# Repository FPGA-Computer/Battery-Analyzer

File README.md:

This is a Dual Channel Battery Analyzer for HaD 2015 Contest Entry.

+ Ver 2.1 Rel 0/	
|  |Initial PCB release - first layout/non-tested
|  |
|  + Eagle PCB/
|  | Eagle CAd files
|  |
|  + Sketch3D/
|  | Sketch3D model
|  |
|  + LTSpice/
|    Linear Tech Spice Simulation analog file
|
+ Windows/
| Pelles C Project file
|
+ Firmware/
  Simplicity Studio files

Hackaday project page is at 
https://hackaday.io/project/4993-dual-channel-battery-chargeranalyzer

The hardware design is under a Creative Commons Attribution-
NonCommercial-ShareAlike 4.0 International License.

The full detail of this license is available at: 
http://creativecommons.org/licenses/by-nc-sa/4.0/

The software is under Mozilla Public License
The full detail of this license is available at: 
https://www.mozilla.org/MPL/

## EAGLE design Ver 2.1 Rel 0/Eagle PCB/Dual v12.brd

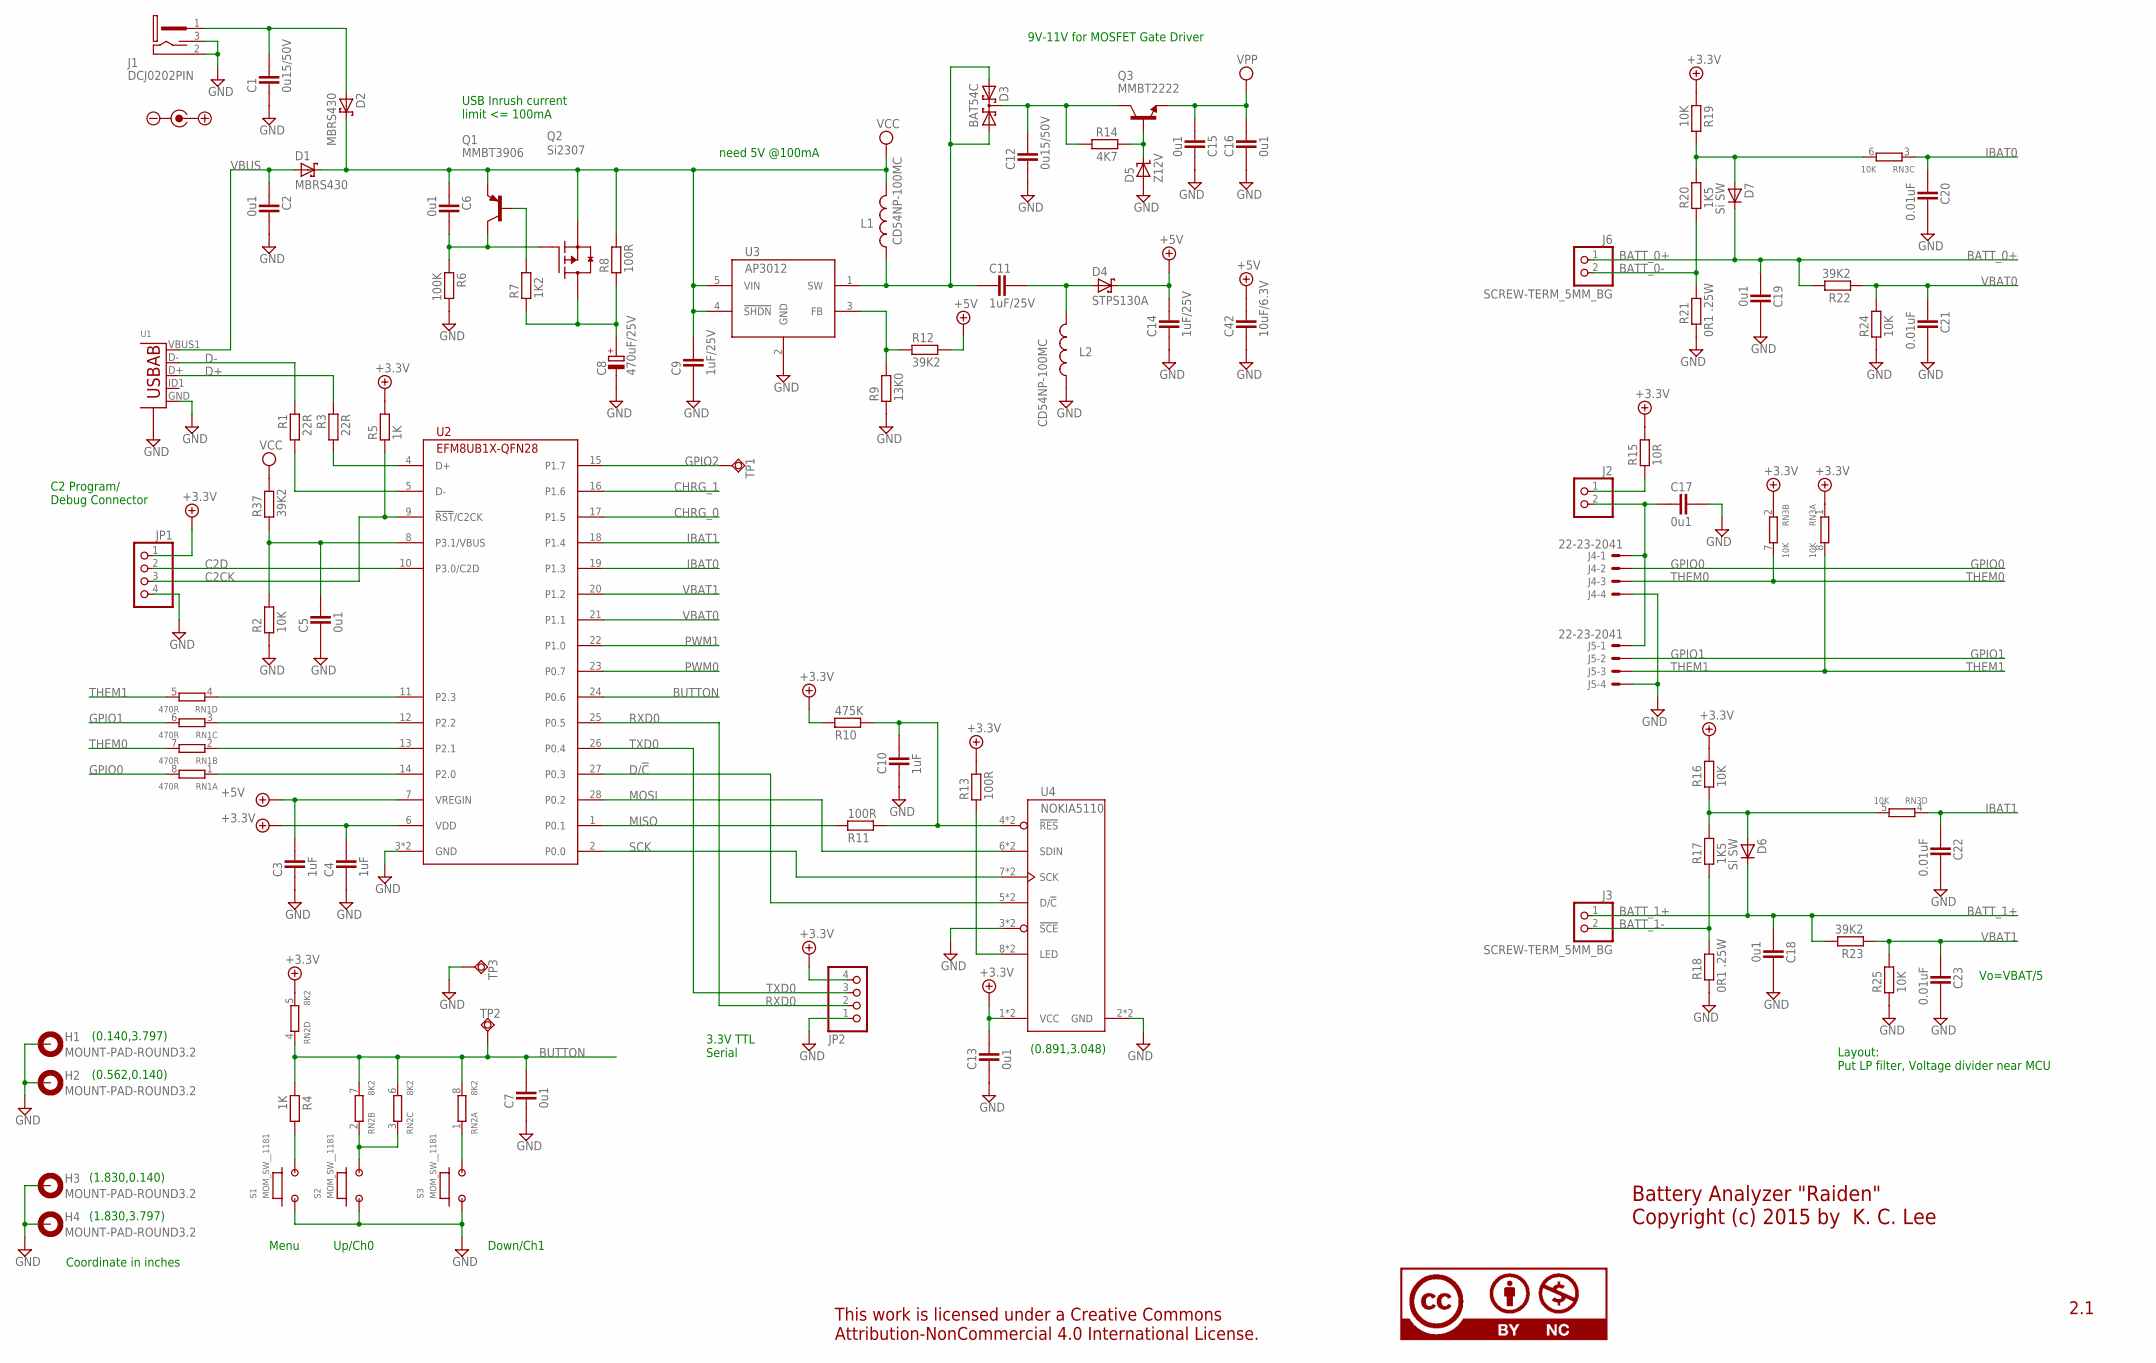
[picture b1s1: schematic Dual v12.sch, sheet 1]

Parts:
C1, C12: 0u15/50V; CAP2012X70N; PARTNO STOCK: 0.15UF/50V10%
C2, C6, C7, C13, C15, C16, C17, C18, C19: 0u1; CAPC1608X92N; PARTNO STOCK: DK 490-1532-1-ND
C3, C4: 1uF; CAPC1005X60N; PARTNO DK: 490-10435-1-ND
C5: 0u1; CAPC1005X60N; PARTNO STOCK: DK 587-1227-1-ND
C8: 470uF/25V; CAPAE1030X1020N; PARTNO STOCK
C9, C11, C14: 1uF/25V; CAP2012X70N; PARTNO DK: 311-1456-1-ND
C10: 1uF; CAPC1608X92N; PARTNO STOCK: 1UF/10V 20% TDK
C20, C21, C22, C23: 0.01uF; CAPC1608X92N; PARTNO DK: 311-1085-1-ND
C42: 10uF/6.3V; CAP2012X70N; PARTNO DK: 490-5525-1-ND
D1, D2: MBRS430; DIOM7959X265N; PARTNO STOCK
D3: BAT54C; SOT95P280X135-3N; PARTNO STOCK
D4: STPS130A; DIOM5326X292N; PARTNO DK: 497-3755-1-ND
D5: Z12V; SOT95P280X135-3N; PARTNO STOCK
D6, D7: Si SW; SOT95P280X135-3N; PARTNO STOCK: BAV99
H1, H2, H3, H4: MOUNT-PAD-ROUND3.2; 3,2-PAD; PARTNO *
J1: DCJ0202PIN; PJ-102A; PARTNO STOCK: DK CP-102A-ND
J2: PINHD-1X2_2.54; 1X02; PARTNO BG: SKU038984
J3, J6: SCREW-TERM_5MM_BG; 1X02-5MM-BG; PARTNO BG: SKU170379
J4, J5: 22-23-2041; PARTNO DK: A19431-ND
JP1: PINHD-1X4_2.54; 1X04; PARTNO BG: SKU038984
JP2: PINHD-1X4_2.54-90°; 1X04-RA; PARTNO STOCK
L1, L2: CD54NP-100MC; CD54; PARTNO DK: 587-1626-1-ND
Q1: MMBT3906; SOT95P280X135-3N; PARTNO STOCK:MMBT3906
Q2: Si2307; SOT95P280X135-3N; PARTNO STOCK: SI2307DS
Q3: MMBT2222; SOT95P280X135-3N; PARTNO STOCK: MMBT2222
R1, R3: 22R; RESC1608X55N; PARTNO STOCK: DK 1276-3497-1-ND
R2, R16, R19, R24, R25: 10K; RESC1608X55N; PARTNO STOCK: 10K 1%
R4: 1K; RESC1608X55N; PARTNO STOCK: DK 1276-3484-1-ND
R5: 1K; RESC1005X40AN; PARTNO DK: 311-1.00KLRCT-ND
R6: 100K; RESC1608X55N; PARTNO STOCK: DK311-100KHRCT-ND
R7: 1K2; RESC1608X55N; PARTNO STOCK: 1K21 1%
R8: 100R; RESC2012X70N; PARTNO STOCK
R9: 13K0; RESC1608X55N; PARTNO DK: 311-13.0KHRCT-ND
R10: 475K; RESC1608X55N; PARTNO STOCK: P475KHCT-ND
R11, R13: 100R; RESC1608X55N; PARTNO STOCK
R12, R22, R23, R37: 39K2; RESC1608X55N; PARTNO DK: 311-39.2KHRCT-ND
R14: 4K7; RESC1608X55N; PARTNO STOCK:4K75 1%
R15: 10R; RESC1608X55N; PARTNO STOCK: 10R 1%
R17, R20: 1K5; RESC1608X55N; PARTNO STOCK: DKRHM1.50KCFCT-ND
R18, R21: 0R1 .25W; RESC3115X70N; PARTNO STOCK: DK73L4R10JCT-ND
RN1: 470R; CAT16; PARTNO DK: YC164J-470CT-ND
RN2: 8K2; CAT16; PARTNO STOCK
RN3: 10K; CAT16; PARTNO STOCK: DK CAY16-103J4GLFCT-ND
S1, S2, S3: MOM_SW__1181; MOM-1181; PARTNO BG: SKU156899
TP1: TPSQTP08R; TP08R; PARTNO *
TP2, TP3: TPSQTP14SQ; TP14SQ; PARTNO *
U1: USB-ABBG; USB-AB-MICRO-SMD_V03_SF; PARTNO DX: SKU134132
U2: EFM8UB1X-QFN28; QFN-28; PARTNO DK: 336-3183-5-ND
U3: AP3012; SOT23-5; PARTNO DK: AP3012KTR-G1DICT-ND
U4: NOKIA5110; NOKIA5110-BOTH; PARTNO BG: SKU091069
U$1: CC100%; CC-100; PARTNO *
U$3: POLARITY; PARTNO *

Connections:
+3.3V: C4.2, C13.2, JP1.1, JP2.4, R5.2, R10.1, R13.2, R15.2, R16.2, R19.1, RN2.5 (2), RN3.1, RN3.2 (1), U2.6 (VDD), U4.1 (VCC), U4.9 (VCC); also elsewhere on the board
+5V: C3.2, C14.2, C42.2, D4.K, R12.2, U2.7 (VREGIN); also elsewhere on the board
BATT_0+: C19.1, D7.3 (K), J6.1, R22.2; also elsewhere on the board
BATT_0-: J6.2, R20.1, R21.2
BATT_1+: C18.1, D6.3 (K), J3.1, R23.2; also elsewhere on the board
BATT_1-: J3.2, R17.1, R18.2
BUTTON: C7.2, R4.1, RN2.4 (1), RN2.6 (2), RN2.7 (2), RN2.8 (2), TP2.TP, U2.24 (P0.6)
C2CK: JP1.3, R5.1, U2.9 (!RST!/C2CK)
C2D: JP1.2, U2.10 (P3.0/C2D)
CHRG_0: U2.17 (P1.5); also elsewhere on the board
CHRG_1: U2.16 (P1.6); also elsewhere on the board
D+: R3.1, U1.D+
D-: R1.1, U1.D-
D/!C: U2.27 (P0.3), U4.5 (D/!C), U4.13 (D/!C)
GND: C1.1, C2.2, C3.1, C4.1, C5.1, C7.1, C8.-, C9.1, C10.1, C12.1, C13.1, C14.1, C15.1, C16.1, C17.2, C18.2, C19.2, C20.2, C21.2, C22.2, C23.2, C42.1, D5.1 (A), H1.B3,2, H2.B3,2, H3.B3,2, H4.B3,2, J1.2 (3), J1.3 (2), J4.4, J5.4, JP1.4, JP2.1, L2.1, R2.1, R6.2, R9.1, R18.1, R21.1, R24.1, R25.1, S1.1, S2.1, S3.1, TP3.TP, U1.GND, U1.S1 (S), U1.S2 (S), U1.S3 (S), U1.S4 (S), U2.3 (GND), U2.PAD (GND), U3.2 (GND), U4.2 (GND), U4.3 (!SCE), U4.10 (GND), U4.11 (!SCE); also elsewhere on the board
GPIO0: J4.2, RN1.8 (2)
GPIO1: J5.2, RN1.6 (2)
GPIO2: TP1.TP, U2.15 (P1.7)
IBAT0: C20.1, RN3.3 (1), U2.19 (P1.3)
IBAT1: C22.1, RN3.4 (1), U2.18 (P1.4)
MISO: R11.1, U2.1 (P0.1)
MOSI: U2.28 (P0.2), U4.6 (SDIN), U4.14 (SDIN)
unnamed: C6.2, Q1.3 (C), Q2.1 (G), R6.1
unnamed: C10.2, R10.2, R11.2, U4.4 (!RES), U4.12 (!RES)
unnamed: Q1.1 (B), R7.2
unnamed: R13.1, U4.8 (LED), U4.16 (LED)
unnamed: RN1.1, U2.14 (P2.0)
unnamed: C1.2, D2.A, J1.1
unnamed: D5.3 (K), Q3.1 (B), R14.1
unnamed: C11.1, D3.1 (A1), D3.2 (A2), L1.1, U3.1 (SW)
unnamed: C8.+, Q2.3 (D), R7.1, R8.1
unnamed: C11.2, D4.A, L2.2
unnamed: R3.2, U2.4 (D+)
unnamed: C12.2, D3.3 (CC), Q3.3 (C), R14.2
unnamed: R9.2, R12.1, U3.3 (FB)
unnamed: C5.2, R2.2, R37.1, U2.8 (P3.1/VBUS)
unnamed: R1.2, U2.5 (D-)
unnamed: RN1.2 (1), U2.13 (P2.1)
unnamed: R4.2, S1.2
unnamed: RN1.3 (1), U2.12 (P2.2)
unnamed: RN1.4 (1), U2.11 (P2.3)
unnamed: C17.1, J2.2, J4.1, J5.1
unnamed: RN2.2 (1), RN2.3 (1), S2.2
unnamed: J2.1, R15.1
unnamed: RN2.1, S3.2
unnamed: D6.1 (A), R16.1, R17.2, RN3.5 (2)
unnamed: D7.1 (A), R19.2, R20.2, RN3.6 (2)
PWM0: U2.23 (P0.7); also elsewhere on the board
PWM1: U2.22 (P1.0); also elsewhere on the board
RXD0: JP2.2, U2.25 (P0.5)
SCK: U2.2 (P0.0), U4.7 (SCK), U4.15 (SCK)
THEM0: J4.3, RN1.7 (2), RN3.7 (2)
THEM1: J5.3, RN1.5 (2), RN3.8 (2)
TXD0: JP2.3, U2.26 (P0.4)
VBAT0: C21.1, R22.1, R24.2, U2.21 (P1.1)
VBAT1: C23.1, R23.1, R25.2, U2.20 (P1.2)
VBUS: C2.1, D1.A, U1.VBUS1 (VBUS)
VCC: C6.1, C9.2, D1.K, D2.K, L1.2, Q1.2 (E), Q2.2 (S), R8.2, R37.2, U3.4 (!SHDN), U3.5 (VIN); also elsewhere on the board
VPP: C15.2, C16.2, Q3.2 (E); also elsewhere on the board

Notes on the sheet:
USB Inrush current limit <= 100mA
need 5V @100mA
C2 Program/ Debug Connector
3.3V TTL Serial
Vo=VBAT/5
(0.140,3.797)
(0.562,0.140)
(1.830,0.140)
(1.830,3.797)
Layout: Put LP filter, Voltage divider near MCU
Menu
Up/Ch0
Down/Ch1
Battery Analyzer "Raiden" Copyright (c) 2015 by K. C. Lee
9V-11V for MOSFET Gate Driver
2.1
Coordinate in inches
(0.891,3.048)

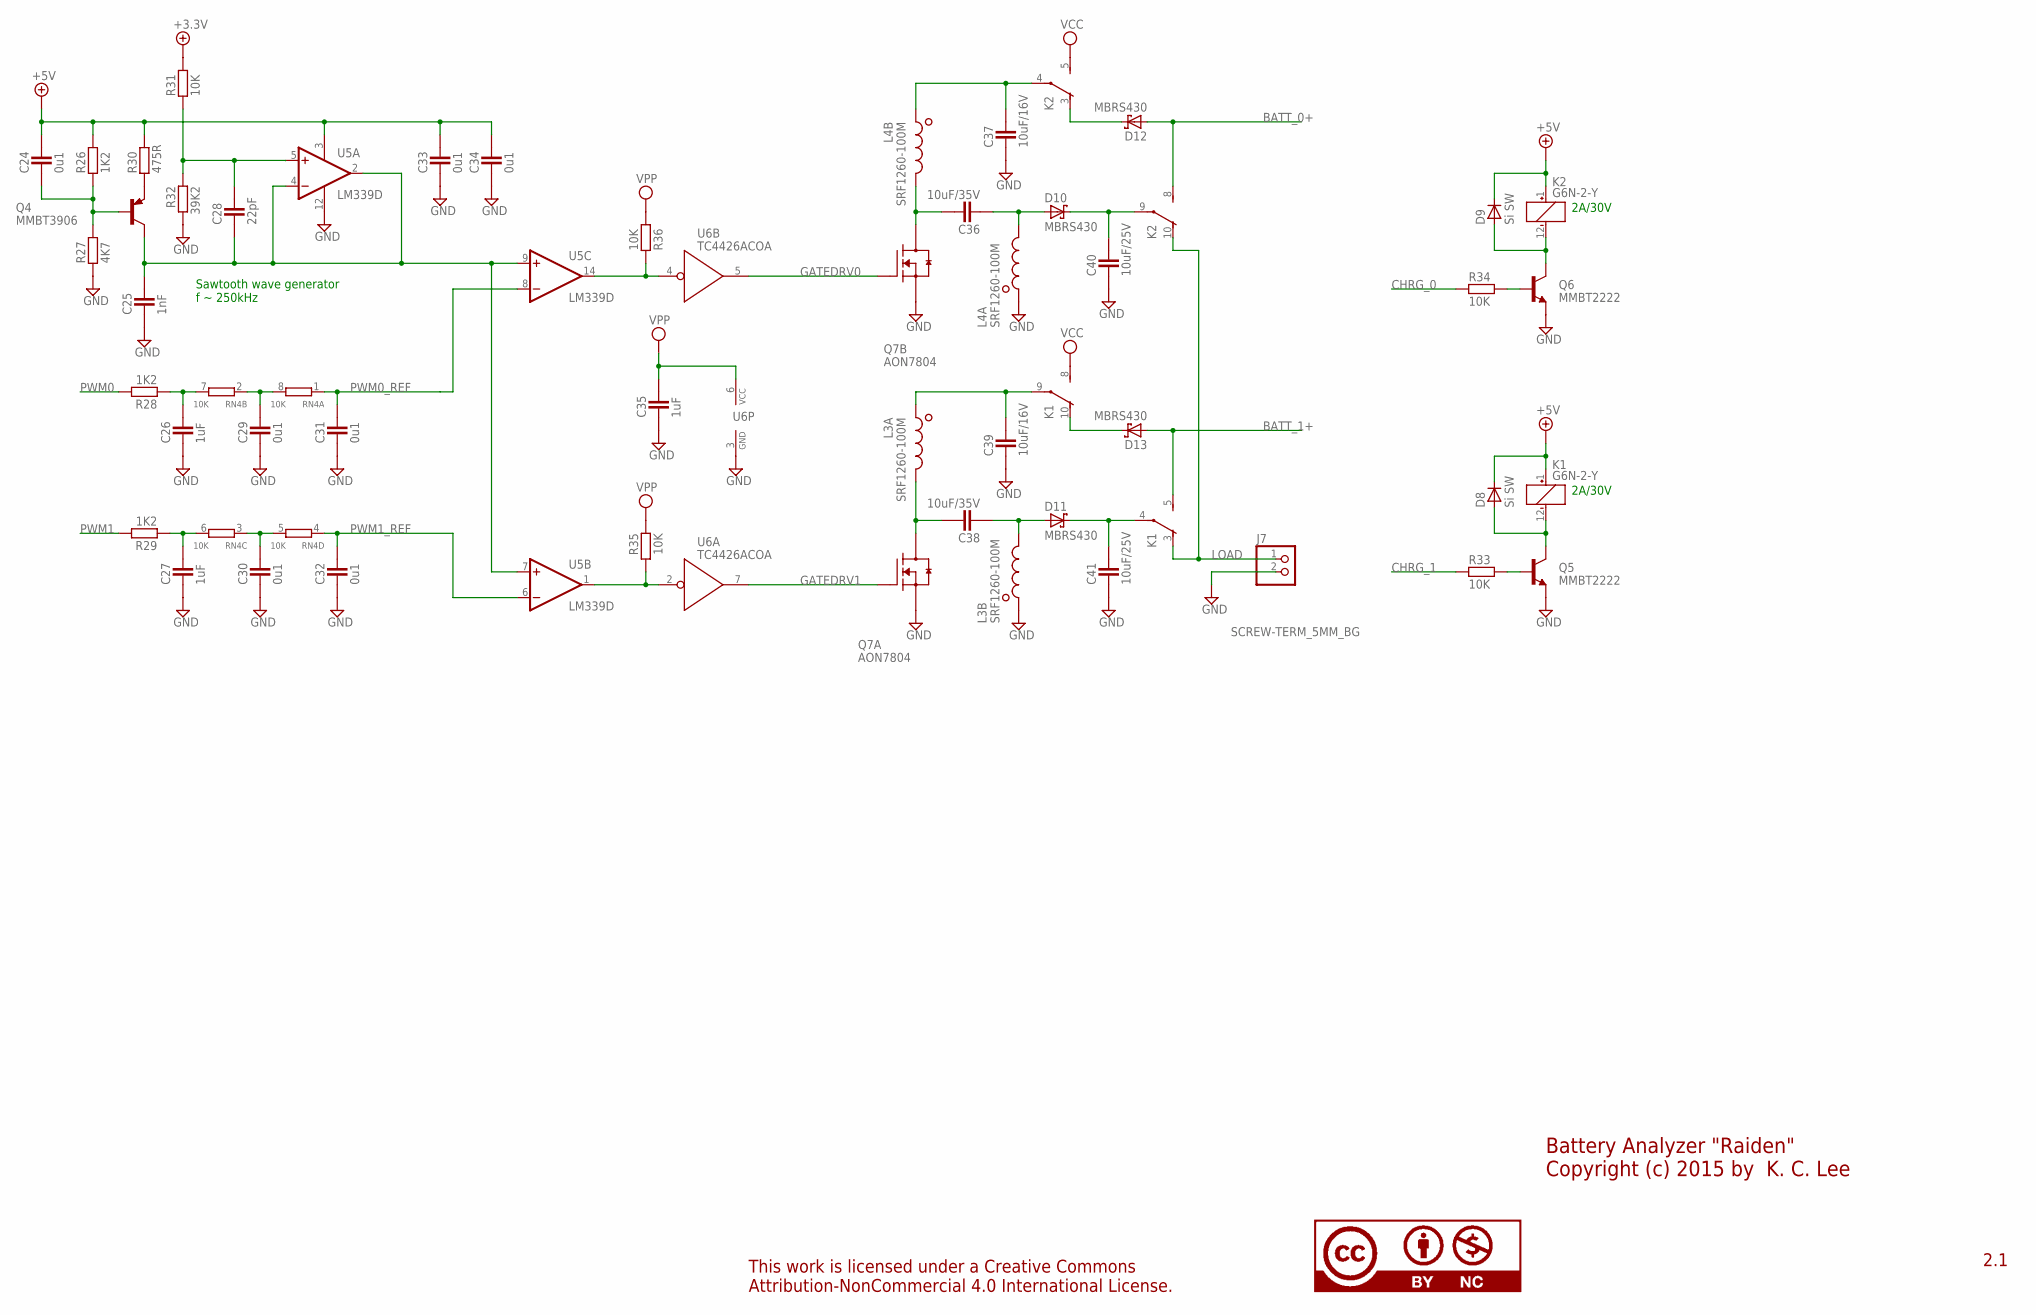
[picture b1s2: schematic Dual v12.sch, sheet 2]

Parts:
C24, C33, C34: 0u1; CAPC1608X92N; PARTNO STOCK: DK 490-1532-1-ND
C25: 1nF; CAPC1608X92N; PARTNO DK: 311-1080-1-ND
C26, C27, C35: 1uF; CAPC1608X92N; PARTNO STOCK: 1UF/10V 20% TDK
C28: 22pF; CAPC1608X92N; PARTNO STOCK: 22PF
C29, C30, C31, C32: 0u1; CAPC1005X60N; PARTNO STOCK: DK 587-1227-1-ND
C36, C38: 10uF/35V; CAPC3215X168N; PARTNO DK: 490-9964-1-ND
C37, C39: 10uF/16V; CAPC3215X168N; PARTNO DK: 490-5525-1-ND
C40, C41: 10uF/25V; CAPC3215X168N; PARTNO DK: 490-5525-1-ND
D8, D9: Si SW; SOT95P280X135-3N; PARTNO STOCK: BAV99
D10, D11, D12, D13: MBRS430; DIOM7959X265N; PARTNO STOCK
J7: SCREW-TERM_5MM_BG; 1X02-5MM-BG; PARTNO BG: SKU170379
K1, K2: G6N-2-Y; NA; PARTNO STOCK
L3, L4: SRF1260-100M; SRF1260; PARTNO DK: SRF1260-100MCT-ND
Q4: MMBT3906; SOT95P280X135-3N; PARTNO STOCK:MMBT3906
Q5, Q6: MMBT2222; SOT95P280X135-3N; PARTNO STOCK: MMBT2222
Q7: AON7804; DFN3X3; PARTNO DK: 785-1586-1-ND
R26, R28, R29: 1K2; RESC1608X55N; PARTNO STOCK: 1K21 1%
R27: 4K7; RESC1608X55N; PARTNO STOCK:4K75 1%
R30: 475R; RESC1608X55N; PARTNO STOCK: DK 1276-4620-1-ND
R31, R33, R34, R35, R36: 10K; RESC1608X55N; PARTNO STOCK: 10K 1%
R32: 39K2; RESC1608X55N; PARTNO DK: 311-39.2KHRCT-ND
RN4: 10K; CAT16; PARTNO STOCK: DK CAY16-103J4GLFCT-ND
U5: LM339D; SO14; PARTNO STOCK
U6: TC4426ACOA; SOIC8; PARTNO DK: TC4426ACOA-ND
U$2: CCNONE; CC-NONE; PARTNO *

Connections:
+3.3V: R31.2; also elsewhere on the board
+5V: C24.2, C33.2, C34.2, D8.3 (K), D9.3 (K), K1.1 (+), K2.1 (+), R26.2, R30.2, U5.3 (V+); also elsewhere on the board
BATT_0+: D12.A, K2.8 (S); also elsewhere on the board
BATT_1+: D13.A, K1.5 (S); also elsewhere on the board
CHRG_0: R34.1; also elsewhere on the board
CHRG_1: R33.1; also elsewhere on the board
GATEDRV0: Q7.G2 (G), U6.5 (OUT)
GATEDRV1: Q7.G1 (G), U6.7 (OUT)
GND: C25.1, C26.1, C27.1, C29.1, C30.1, C31.1, C32.1, C33.1, C34.1, C35.1, C37.1, C39.1, C40.1, C41.1, J7.2, L3.2 (1), L4.1, Q5.2 (E), Q6.2 (E), Q7.S1 (S), Q7.S2 (S), R27.1, R32.2, U5.12 (GND), U6.3 (GND); also elsewhere on the board
LOAD: J7.1, K1.3 (O), K2.10 (O)
unnamed: D8.1 (A), K1.12 (-), Q5.3 (C)
unnamed: D13.K, K1.10 (O)
unnamed: D9.1 (A), K2.12 (-), Q6.3 (C)
unnamed: C28.2, R31.1, R32.1, U5.5 (+IN)
unnamed: Q6.1 (B), R34.2
unnamed: Q5.1 (B), R33.2
unnamed: D12.K, K2.3 (O)
unnamed: C30.2, RN4.3 (1), RN4.5 (2)
unnamed: C26.2, R28.1, RN4.7 (2)
unnamed: C27.2, R29.1, RN4.6 (2)
unnamed: C29.2, RN4.2 (1), RN4.8 (2)
unnamed: C38.2, L3.3 (2), Q7.D1@1 (D), Q7.D1@2 (D)
unnamed: C24.1, Q4.1 (B), R26.1, R27.2
unnamed: Q4.2 (E), R30.1
unnamed: C25.2, C28.1, Q4.3 (C), U5.2 (OUT), U5.4 (-IN), U5.7 (+IN), U5.9 (+IN)
unnamed: C36.2, L4.4 (2), Q7.D2@1 (D), Q7.D2@2 (D)
unnamed: C38.1, D11.A, L3.4 (2)
unnamed: C36.1, D10.A, L4.3 (2)
unnamed: C37.2, K2.4, L4.2 (1)
unnamed: C40.2, D10.K, K2.9
unnamed: C41.2, D11.K, K1.4
unnamed: C39.2, K1.9, L3.1
PWM0: R28.2; also elsewhere on the board
PWM0_OUT: R35.2, U5.1 (OUT), U6.2 (!IN)
PWM0_REF: C31.2, RN4.1, U5.8 (-IN)
PWM1: R29.2; also elsewhere on the board
PWM1_OUT: R36.1, U5.14 (OUT), U6.4 (!IN)
PWM1_REF: C32.2, RN4.4 (1), U5.6 (-IN)
VCC: K1.8 (S), K2.5 (S); also elsewhere on the board
VPP: C35.2, R35.1, R36.2, U6.6 (VCC); also elsewhere on the board

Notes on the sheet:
Sawtooth wave generator f ~ 250kHz
2A/30V
Battery Analyzer "Raiden" Copyright (c) 2015 by K. C. Lee
2.1

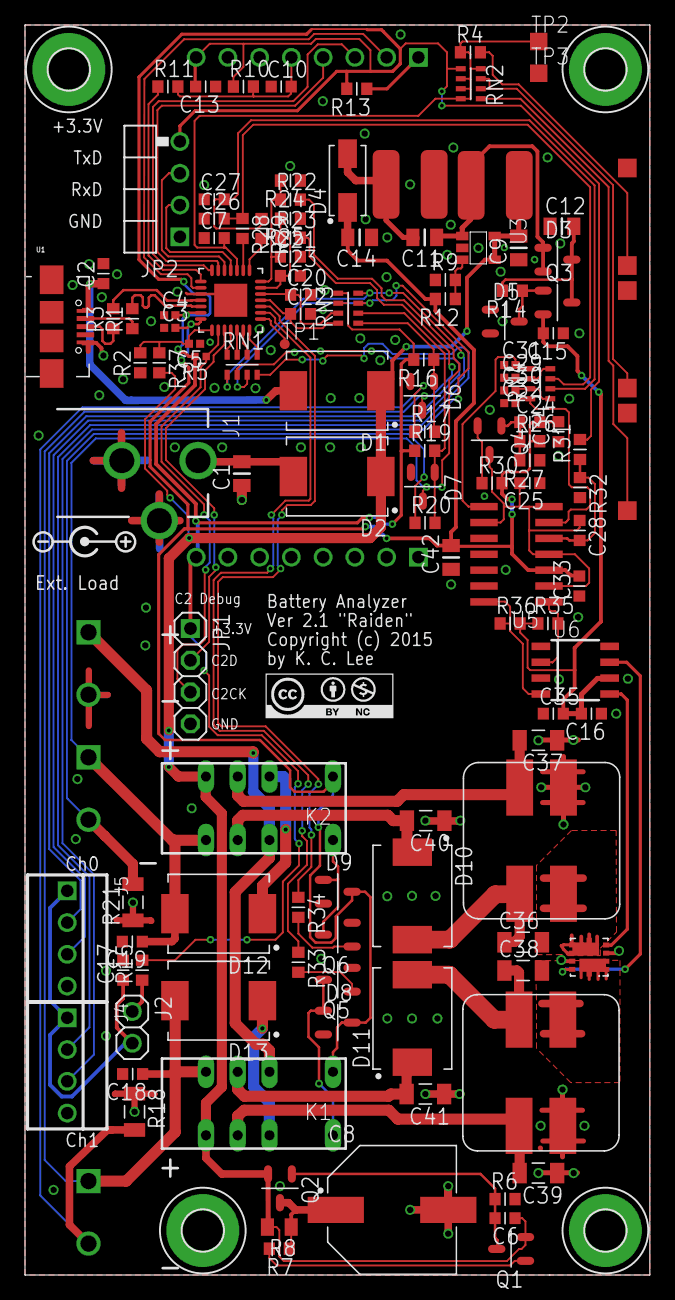
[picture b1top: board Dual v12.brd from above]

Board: 2 copper layers, 50.0 x 100.0 mm, 137 parts (0 on the bottom side), 88 nets.

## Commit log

2015-07-23 Initial Commit - PCB Ordered/Release - non tested
2015-07-23 fix readme.md
2015-07-23 Add LTSpice,, pdf schematic
2015-08-27 Initial Windows Most Software release
2015-08-27 fixed README.md spelling
2015-09-12 added BOM
2015-09-12 added BOM - take 2

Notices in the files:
parts and their libraries:
Misc logo: This work is licensed under a Creative Commons
Attribution-NonCommercial 4.0 International License.
